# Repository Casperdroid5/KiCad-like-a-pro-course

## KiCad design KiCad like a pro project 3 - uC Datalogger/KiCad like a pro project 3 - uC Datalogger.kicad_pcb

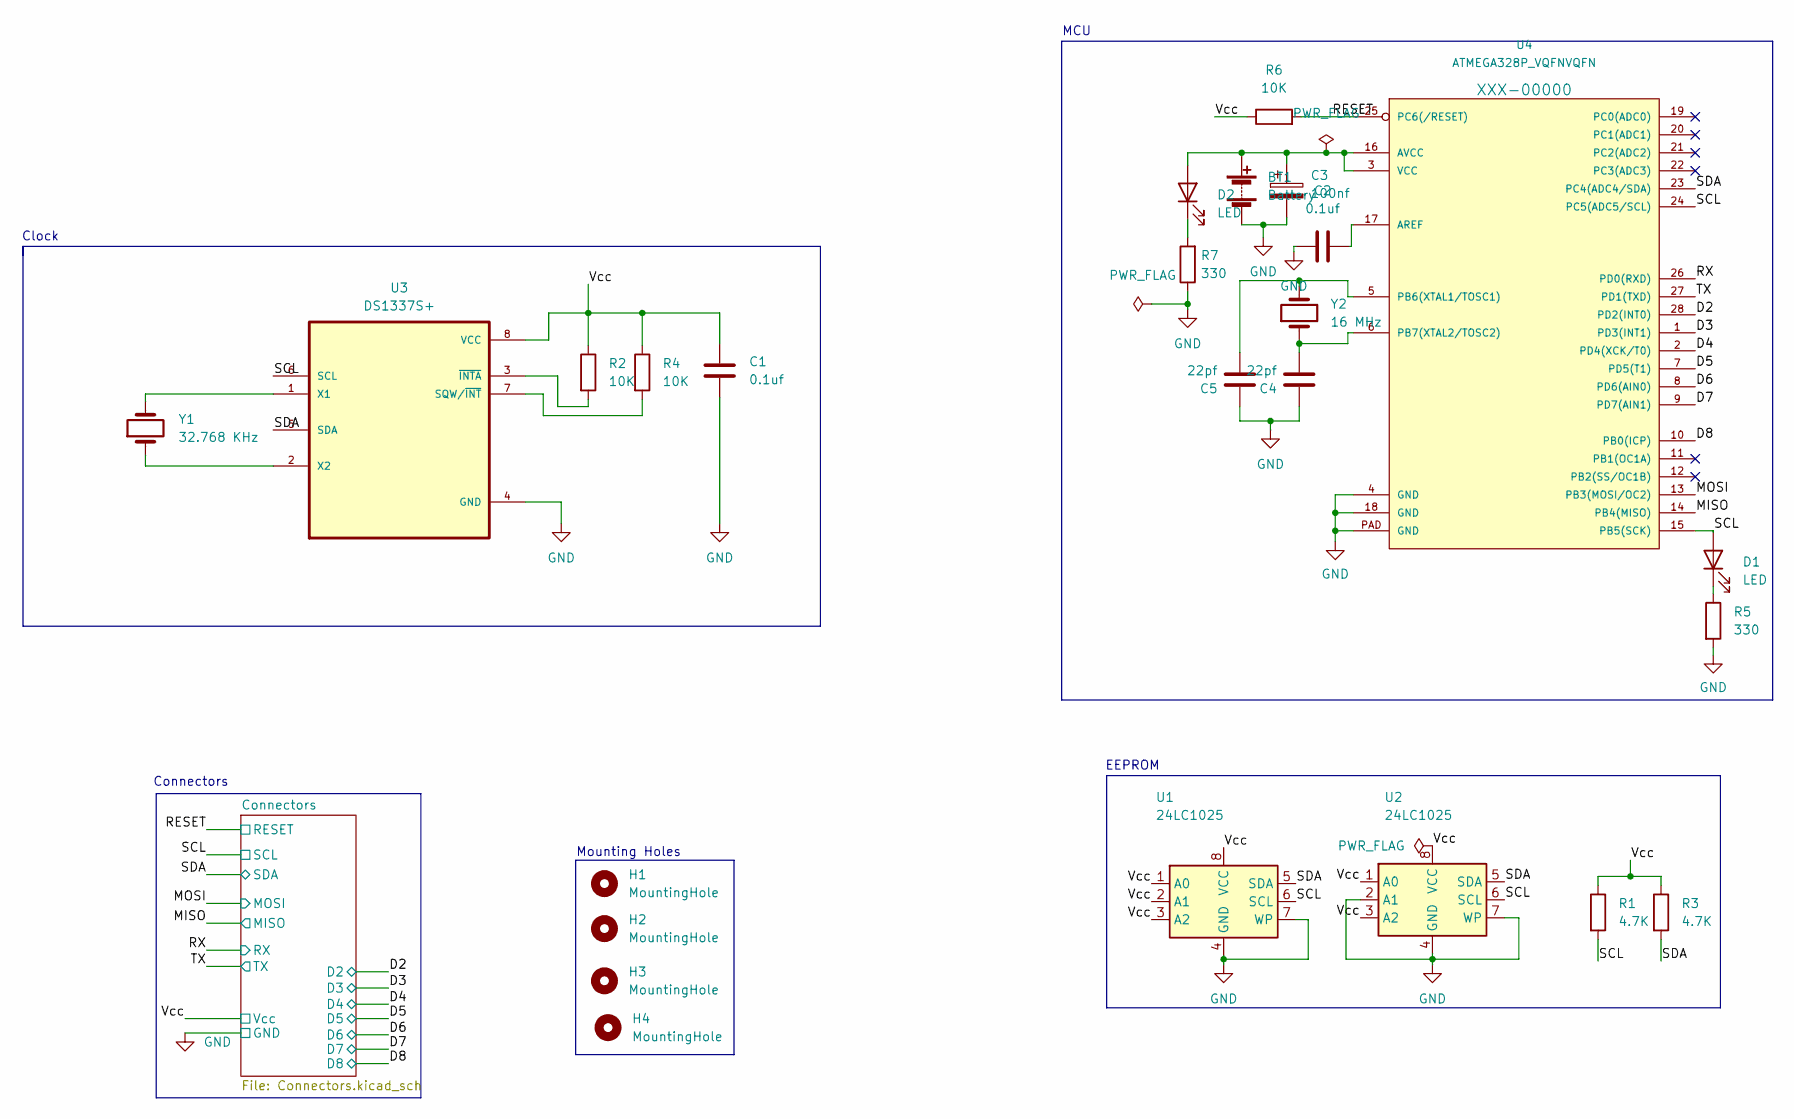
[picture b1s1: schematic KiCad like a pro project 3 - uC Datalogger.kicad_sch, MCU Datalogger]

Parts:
BT1: Battery; PinHeader_1x02_P2.54mm_Vertical
C1, C2: 0.1uf; C_0805_2012Metric
C3: 100nf; C_0805_2012Metric
C4, C5: 22pf; C_0805_2012Metric
D1, D2: LED; LED_0805_2012Metric
H1, H2, H3, H4: MountingHole; MountingHole_2.1mm
R1, R3: 4.7K; R_0805_2012Metric
R2, R4, R6: 10K; R_0805_2012Metric
R5, R7: 330; R_0805_2012Metric
U1, U2: 24LC1025; SOIC-8_5.23x5.23mm_P1.27mm
U3: DS1337S+; SOIC127P600X175-8N
U4: ATMEGA328P_VQFNVQFN; QFP80P900X900X120-32N
Y1: 32.768 KHz; Crystal_SMD_5032-2Pin_5.0x3.2mm_HandSoldering
Y2: 16 MHz; Crystal_SMD_5032-2Pin_5.0x3.2mm_HandSoldering

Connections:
/D2: U4.28 (PD2(INT0)); also elsewhere on the board
/D3: U4.1 (PD3(INT1)); also elsewhere on the board
/D4: U4.2 (PD4(XCK/T0)); also elsewhere on the board
/D5: U4.7 (PD5(T1)); also elsewhere on the board
/D6: U4.8 (PD6(AIN0)); also elsewhere on the board
/D7: U4.9 (PD7(AIN1)); also elsewhere on the board
/D8: U4.10 (PB0(ICP)); also elsewhere on the board
/MISO: U4.14 (PB4(MISO)); also elsewhere on the board
/MOSI: U4.13 (PB3(MOSI/OC2)); also elsewhere on the board
/RESET: R6.2, U4.25 (PC6(/RESET)); also elsewhere on the board
/RX: U4.26 (PD0(RXD)); also elsewhere on the board
/SCL: D1.2 (A), R1.2, U1.6 (SCL), U2.6 (SCL), U3.6 (SCL), U4.15 (PB5(SCK)), U4.24 (PC5(ADC5/SCL)); also elsewhere on the board
/SDA: R3.2, U1.5 (SDA), U2.5 (SDA), U3.5 (SDA), U4.23 (PC4(ADC4/SDA)); also elsewhere on the board
/TX: U4.27 (PD1(TXD)); also elsewhere on the board
/Vcc: C1.1, R1.1, R2.1, R3.1, R4.1, R6.1, U1.1 (A0), U1.2 (A1), U1.3 (A2), U1.8 (VCC), U2.1 (A0), U2.3 (A2), U2.8 (VCC), U3.8 (VCC); also elsewhere on the board
GND: BT1.2 (-), C1.2, C2.1, C3.2, C4.1, C5.1, R5.2, R7.1, U1.4 (GND), U1.7 (WP), U2.2 (A1), U2.4 (GND), U2.7 (WP), U3.4 (GND), U4.4 (GND), U4.18 (GND), U4.PAD (GND); also elsewhere on the board
unnamed: BT1.1 (+), C3.1, D2.2 (A), U4.3 (VCC), U4.16 (AVCC)
unnamed: D1.1 (K), R5.1
unnamed: D2.1 (K), R7.2
unnamed: R2.2, U3.3 (~INTA)
unnamed: R4.2, U3.7 (SQW/~INT)
unnamed: U3.1 (X1), Y1.2
unnamed: U3.2 (X2), Y1.1
unnamed: C5.2, U4.5 (PB6(XTAL1/TOSC1)), Y2.2
unnamed: C4.2, U4.6 (PB7(XTAL2/TOSC2)), Y2.1
unnamed: C2.2, U4.17 (AREF)

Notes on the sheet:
Connectors
Mounting Holes
EEPROM
Clock
MCU

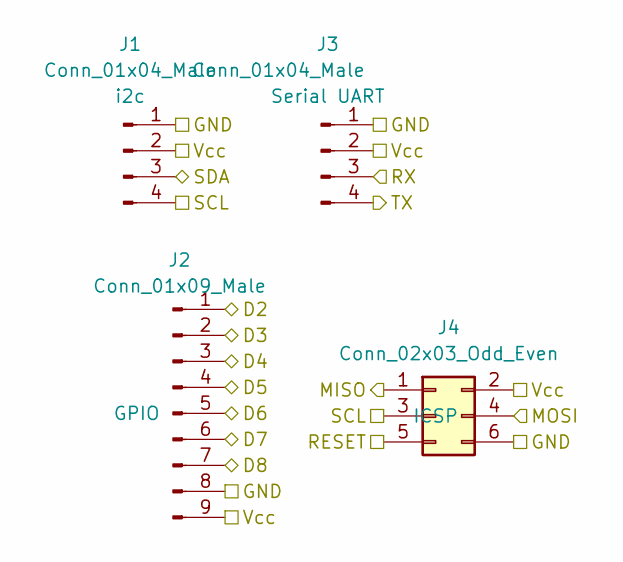
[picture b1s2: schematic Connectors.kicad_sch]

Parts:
J1, J3: Conn_01x04_Male; PinHeader_1x04_P2.54mm_Vertical
J2: Conn_01x09_Male; PinHeader_1x09_P2.54mm_Vertical
J4: Conn_02x03_Odd_Even; PinHeader_2x03_P2.54mm_Vertical

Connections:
/D2: J2.1; also elsewhere on the board
/D3: J2.2; also elsewhere on the board
/D4: J2.3; also elsewhere on the board
/D5: J2.4; also elsewhere on the board
/D6: J2.5; also elsewhere on the board
/D7: J2.6; also elsewhere on the board
/D8: J2.7; also elsewhere on the board
/MISO: J4.1; also elsewhere on the board
/MOSI: J4.4; also elsewhere on the board
/RESET: J4.5; also elsewhere on the board
/RX: J3.3; also elsewhere on the board
/SCL: J1.4, J4.3; also elsewhere on the board
/SDA: J1.3; also elsewhere on the board
/TX: J3.4; also elsewhere on the board
/Vcc: J1.2, J2.9, J3.2, J4.2; also elsewhere on the board
GND: J1.1, J2.8, J3.1, J4.6; also elsewhere on the board

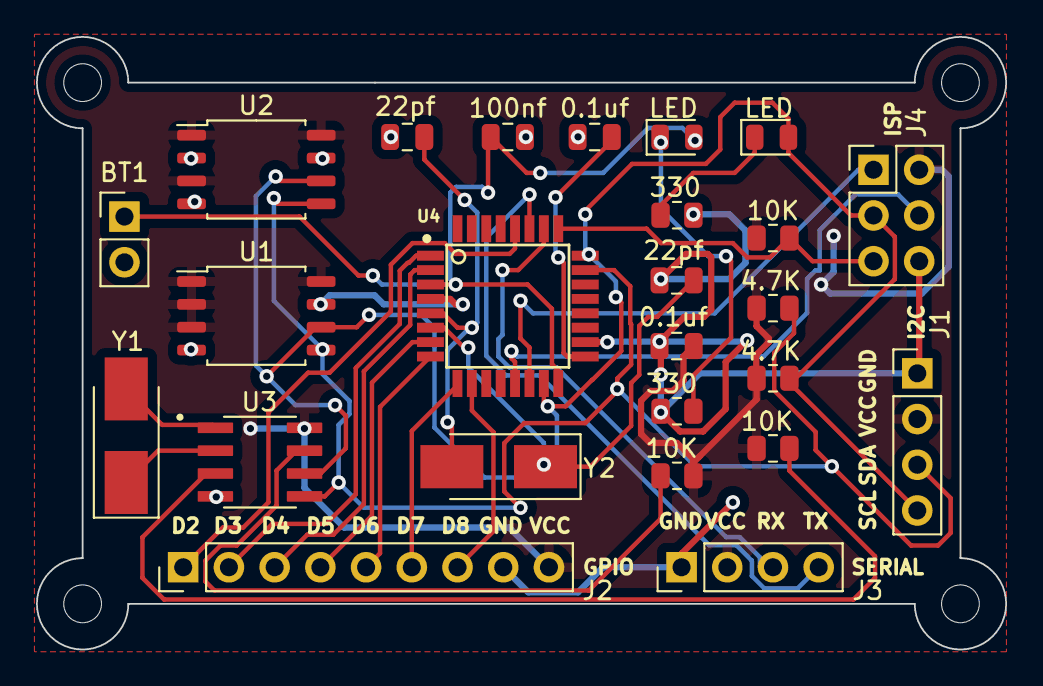
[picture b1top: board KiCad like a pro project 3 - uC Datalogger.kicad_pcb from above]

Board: 2 copper layers, 53.8 x 34.0 mm, 29 parts (0 on the bottom side), 26 nets.

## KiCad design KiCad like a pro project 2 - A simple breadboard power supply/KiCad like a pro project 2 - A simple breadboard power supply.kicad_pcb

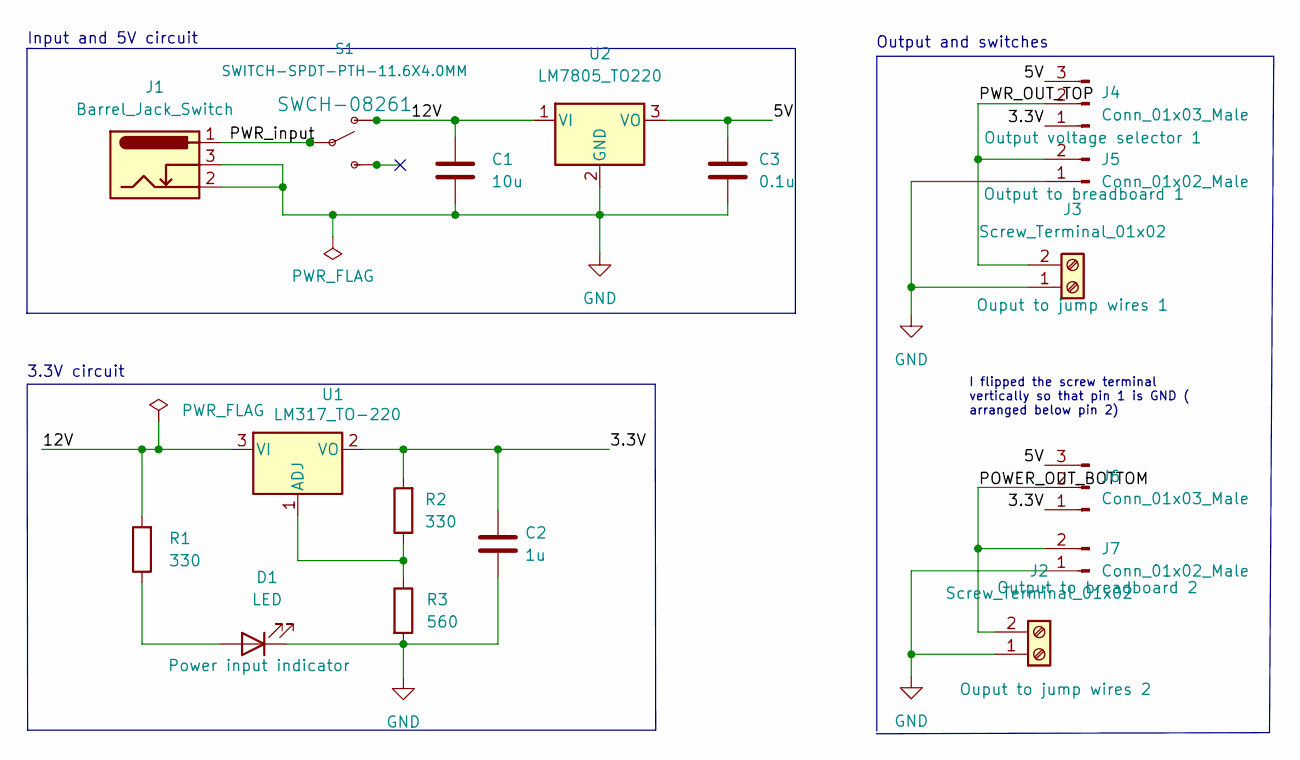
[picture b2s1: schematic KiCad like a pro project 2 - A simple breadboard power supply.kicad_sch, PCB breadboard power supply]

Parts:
C1: 10u; R_Axial_DIN0204_L3.6mm_D1.6mm_P7.62mm_Horizontal
C2: 1u; C_Disc_D3.0mm_W1.6mm_P2.50mm
C3: 0.1u; C_Disc_D3.0mm_W1.6mm_P2.50mm
D1: LED; LED_D5.0mm
J1: Barrel_Jack_Switch; BarrelJack_Horizontal
J2, J3: Screw_Terminal_01x02; TerminalBlock_bornier-2_P5.08mm
J4, J6: Conn_01x03_Male; PinSocket_1x03_P2.54mm_Vertical
J5, J7: Conn_01x02_Male; PinSocket_1x02_P2.54mm_Vertical
R1, R2: 330; R_Axial_DIN0204_L3.6mm_D1.6mm_P7.62mm_Horizontal
R3: 560; R_Axial_DIN0204_L3.6mm_D1.6mm_P7.62mm_Horizontal
S1: SWITCH-SPDT-PTH-11.6X4.0MM; SW_Slide_1P2T_CK_OS102011MS2Q
U1: LM317_TO-220; TO-220-3_Vertical
U2: LM7805_TO220; TO-220-3_Vertical

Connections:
/3.3V: C2.1, J4.1, J6.1, R2.2, U1.2 (VO)
/5V: C3.1, J4.3, J6.3, U2.3 (VO)
/12V: C1.1, R1.2, S1.1 (O), U1.3 (VI), U2.1 (VI)
/POWER_OUT_BOTTOM: J2.2, J6.2, J7.2
/PWR_input: J1.1, S1.2
GND: C1.2, C2.2, C3.2, D1.1 (K), J1.2, J1.3, J2.1, J3.1, J5.1, J7.1, R3.2, U2.2 (GND)
unnamed: D1.2 (A), R1.1
unnamed: J3.2, J4.2, J5.2
unnamed: R2.1, R3.1, U1.1 (ADJ)

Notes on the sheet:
Input and 5V circuit
Output and switches
3.3V circuit
I flipped the screw terminal vertically so that pin 1 is GND ( arranged below pin 2)

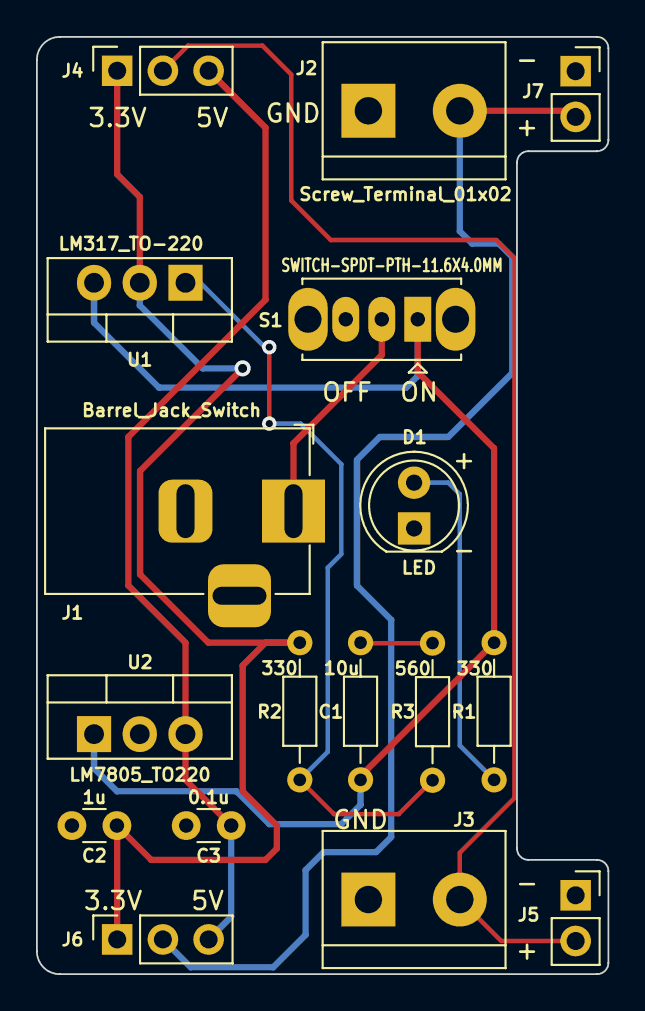
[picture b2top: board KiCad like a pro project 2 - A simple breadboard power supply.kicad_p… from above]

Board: 2 copper layers, 31.8 x 52.1 mm, 17 parts (0 on the bottom side), 9 nets.

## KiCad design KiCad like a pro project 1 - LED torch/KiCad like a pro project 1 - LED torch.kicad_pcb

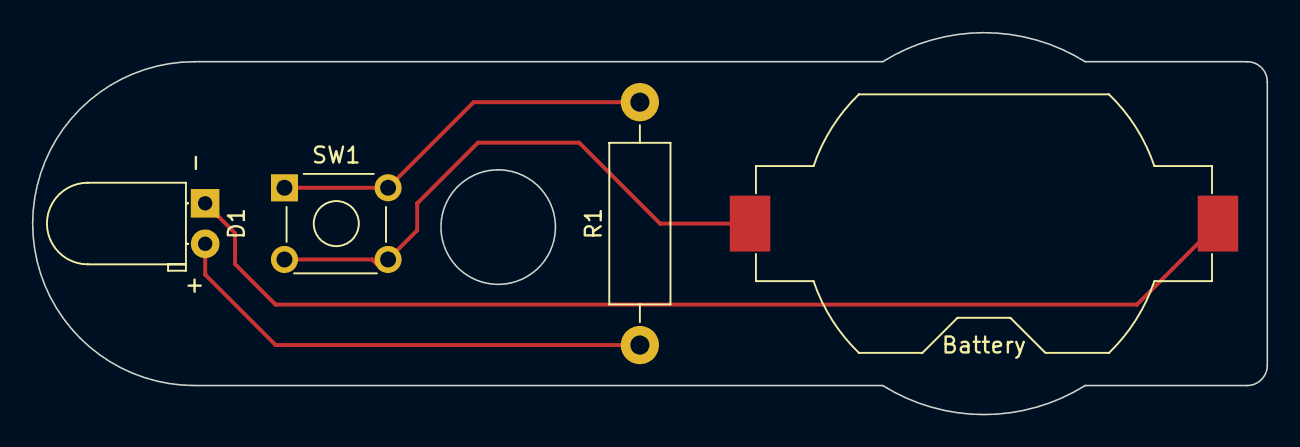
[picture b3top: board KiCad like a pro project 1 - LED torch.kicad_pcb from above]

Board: 2 copper layers, 77.5 x 24.0 mm, 4 parts (0 on the bottom side), 4 nets.

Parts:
Battery: Battery_Cell; BatteryHolder_Keystone_1058_1x2032
D1: LED; LED_D5.0mm_Horizontal_O1.27mm_Z3.0mm
R1: R; R_Axial_DIN0411_L9.9mm_D3.6mm_P15.24mm_Horizontal
SW1: SW_DPST_x2; SW_TH_Tactile_Omron_B3F-10xx

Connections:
/LED_anode: D1.2 (A), R1.1
/LED_cathode: Battery.2 (-), D1.1 (K)
/bat_pos: Battery.1 (+), SW1.2 (B)
unnamed: R1.2, SW1.1 (A)

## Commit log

2022-07-29 Project 1 and 2
    Light torch and breadboard PSU
2022-07-29 first commit project 3
2022-07-31 components placed
2022-07-31 changed locations of symbols (arrange)
2022-07-31 added component values
2022-07-31 completed symbol to footprint associations
2022-07-31 Completed wiring of main sheet
2022-07-31 finished wiring on connector sheet
2022-07-31 Allocated GND and VCC nets to the power net class
2022-07-31 Completed comments
2022-07-31 enh schematic layout
2022-07-31 enh layout and text schematic
2022-07-31 Setup PCBNew
2022-08-04 completed placement of foodprints
2022-08-04 Started wiring
2022-08-05 Removed wires, redrawn pcb outline
2022-08-05 repositioned some components
2022-08-05 repositioned components and started wiring
2022-08-05 removed wiring
2022-08-05 added front and back silkscreen
2022-08-05 repositioned pcb to center of workfield
2022-08-05 Finished wiring
2022-08-05 added 3d components
2022-08-05 cleanup
2022-08-05 Schematic fault also corrected in 2-layer-pcb
